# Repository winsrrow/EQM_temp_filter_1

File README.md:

# EQM_temp_filter_1
 
 ### Proyecto actualmente paralizado
 
 Proyecto para la actualización de la placa del laboratorio de sistemas y equipos de medida.

Este proyecto se compone de dos circuitos que servirán para la base de los ejercicios de laboratorio.
Para el diseño de esta placa me basaré en los esquemas de los que dispongo proporcionados por la profesora, si bien se pretende
añadir diversas modificaciones para facilitar el entendimiento y el uso, entre otras se añadirá protecciones contra polaridad inversa
e indicadores mediante LEDs.

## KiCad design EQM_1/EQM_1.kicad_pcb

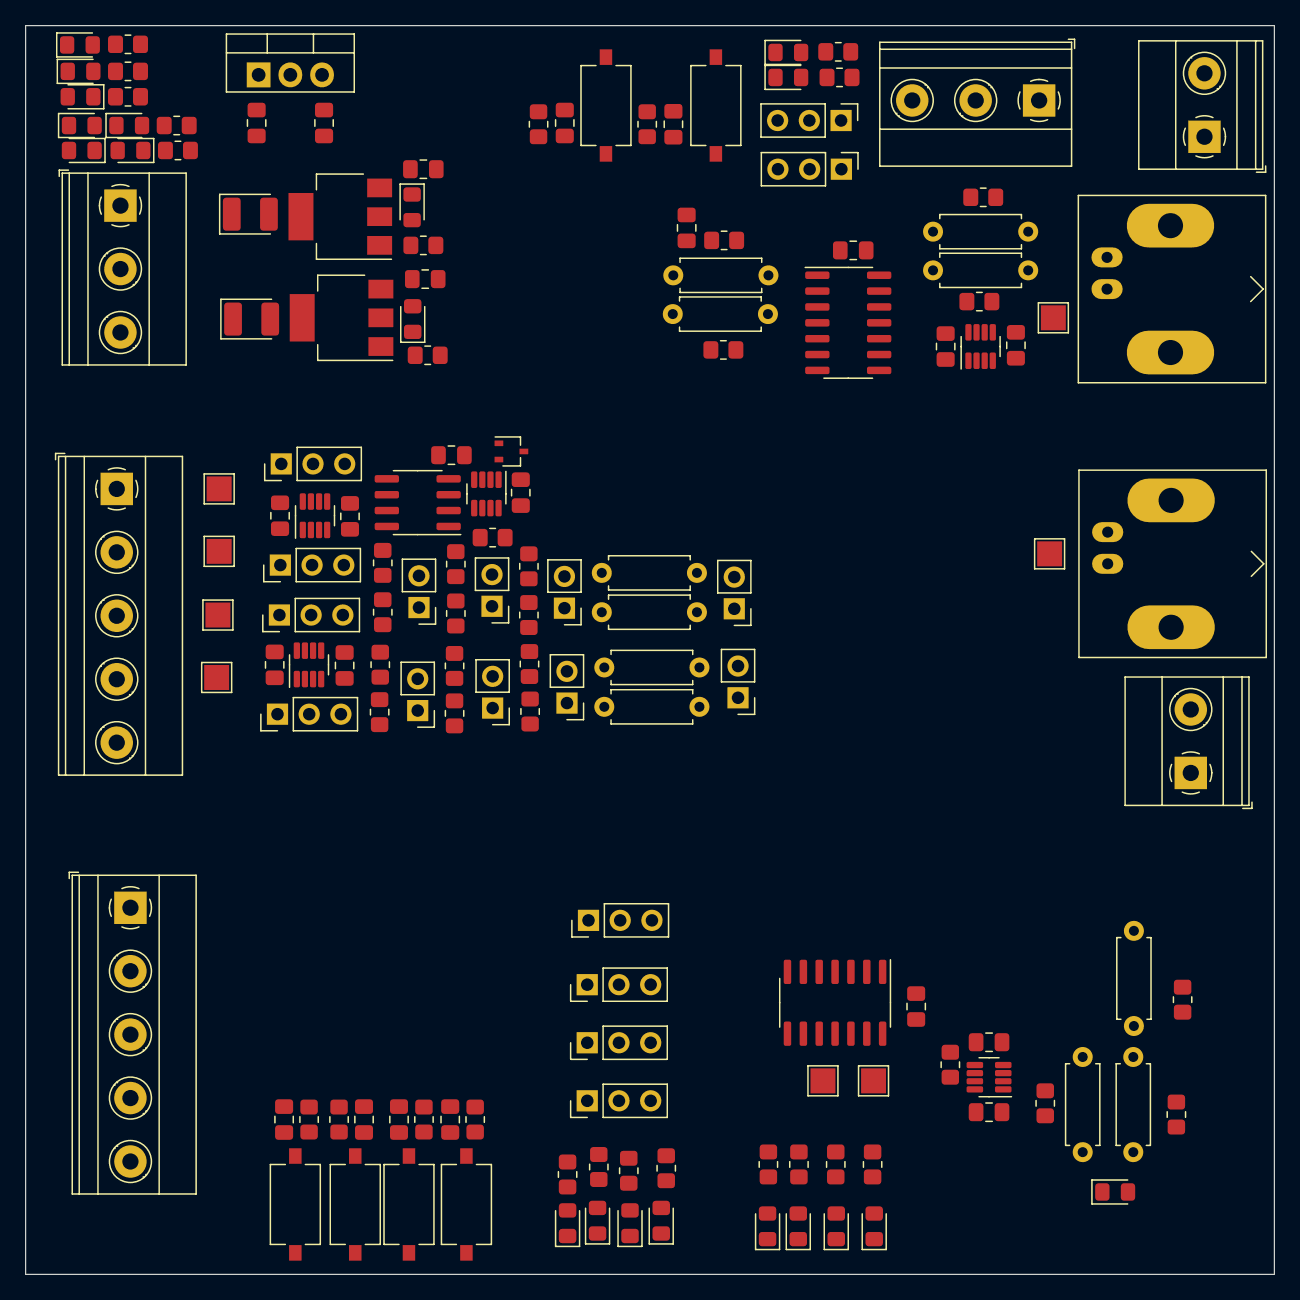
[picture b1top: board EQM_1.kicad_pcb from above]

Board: 2 copper layers, 100.0 x 100.0 mm, 152 parts (0 on the bottom side), 83 nets, no tracks yet.

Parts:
C201, C202, C203, C204: 3.3uF; C_0805_2012Metric_Pad1.18x1.45mm_HandSolder
C301, C302, C303, C304, C305, C306, C401, C402, C403, C404, C405, C406, C501, C502, C503, C504, C505, C506, C507: 100nF; C_0805_2012Metric_Pad1.18x1.45mm_HandSolder
D201, D209: 5.1V; D_0805_2012Metric_Pad1.15x1.40mm_HandSolder
D202, D203, D204, D207, D208, D401, D402, D502, D503, D504, D505, D506, D507, D508, D509: LED_Filled; D_0805_2012Metric_Pad1.15x1.40mm_HandSolder
D205, D206: 1n4007; D_0805_2012Metric_Pad1.15x1.40mm_HandSolder
D501: D_Zener_Filled; D_0805_2012Metric_Pad1.15x1.40mm_HandSolder
F201, F202: 200mA; D_1210_3225Metric_Pad1.42x2.65mm_HandSolder
J201, J407: Screw_Terminal_01x03; TerminalBlock_Phoenix_MKDS-1,5-3-5.08_1x03_P5.08mm_Horizont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
J301, J307, J312, J313, J405, J406, J502, J503, J504, J505: PinHeader_1x03_P2.54mm_Vertical
J302, J501: Screw_Terminal_01x05; TerminalBlock_Phoenix_MKDS-1,5-5-5.08_1x05_P5.08mm_Horizont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
J303, J304, J305, J306, J308, J309, J310, J311: PinHeader_1x02_P2.54mm_Vertical
J401, J403: Conn_Coaxial; BNC_Amphenol_B6252HB-NPP3G-50_Horizontal
J402, J404: Screw_Terminal_01x02; TerminalBlock_Phoenix_MKDS-1,5-2-5.08_1x02_P5.08mm_Horizont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
Q201: Q_PMOS_GDSD; SOT-223
Q202: Q_NMOS_GDSD; SOT-223
R201, R203, R206, R207: 1K5; R_0805_2012Metric_Pad1.20x1.40mm_HandSolder
R202, R409, R410, R511, R512, R513, R514, R515, R516, R517, R518: 670R; R_0805_2012Metric_Pad1.20x1.40mm_HandSolder
R204, R205, R301, R302, R303, R306, R307, R308, R310, R311, R312, R314, R315, R316, R401, R403, R405, R407, R411, R412, R501, R503, R504, R505, R506, R507, R509, R519: 10K; R_0805_2012Metric_Pad1.20x1.40mm_HandSolder
R304, R309, R313, R317, R402, R404, R406, R408, R502, R508, R510: 10K; R_Axial_DIN0207_L6.3mm_D2.5mm_P7.62mm_Horizontal
R305: 18K; R_0805_2012Metric_Pad1.20x1.40mm_HandSolder
SW401, SW402, SW501, SW502, SW503, SW504: SW_Push; SW_Tactile_SPST_NO_Straight_CK_PTS636Sx25SMTRLFS
TP301, TP302, TP303, TP304, TP401, TP402, TP501, TP502: TestPoint_Flag; TestPoint_Pad_2.0x2.0mm
U201: LM7805_TO220; TO-220-3_Vertical
U301: LM35-D; SOIC-8_3.9x4.9mm_P1.27mm
U302, U303, U305, U402, U502: TL082; SOT-23-8
U304: SOT-323_SC-70
U401, U501: CD4066BM; SO-14_3.9x8.65mm_P1.27mm

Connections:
+5V: C202.1, C403.1, C506.1, R202.2, SW401.2, SW402.2, SW501.2, SW502.2, SW503.2, SW504.2, U201.3 (VO), U401.14 (V_{DD}), U501.14 (V_{DD})
/Filtro programable/CS_{1}: J405.1, J407.1
/Filtro programable/CS_{2}: J406.1, J407.2
/Filtro programable/SW_{1}: C405.1, J405.3, R411.1, SW401.1
/Filtro programable/SW_{2}: C406.1, J406.3, R412.1, SW402.1
/Filtro programable/Sig_{IN-Buff}: R405.1, R406.1, R407.1, R408.1, U402.6 (-), U402.7
/Filtro programable/Sig_{IN}: J401.1 (In), J402.1, TP401.1, U402.5 (+)
/Filtro programable/Sig_{Out}: C401.2, J403.1 (In), J404.1, R401.2, R402.2, R403.2, R404.2, TP402.1, U402.1
/Filtro programable/V-: C401.1, U401.1, U401.4, U401.9, U401.10, U402.2 (-)
/Filtro programable/V_{Control-1}: J405.2, R410.1, U401.6, U401.13
/Filtro programable/V_{Control-2}: J406.2, R409.1, U401.5, U401.12
/Sección c/CS_{1}: J501.1, J502.1
/Sección c/CS_{2}: J501.2, J503.1
/Sección c/CS_{3}: J501.3, J504.1
/Sección c/CS_{4}: J501.4, J505.1
/Sección c/SW_{1}: C501.1, J502.3, R503.1, SW501.1
/Sección c/SW_{2}: C502.1, J503.3, R504.1, SW502.1
/Sección c/SW_{3}: C503.1, J504.3, R505.1, SW503.1
/Sección c/SW_{4}: C504.1, J505.3, R506.1, SW504.1
/Sección c/V_{Control-1}: J502.2, R518.1, U501.6, U501.13
/Sección c/V_{Control-2}: J503.2, R517.1, U501.5, U501.12
/Sección c/V_{Control-3}: J504.2, R516.1
/Sección c/V_{Control-4}: J505.2, R515.1
/Sensor de temperatura/L_{ratio-Buff}: J313.1, U305.1, U305.2 (-)
/Sensor de temperatura/L_{ratio-Out}: J302.4, J313.2, TP304.1
/Sensor de temperatura/L_{ratio}: J308.1, J309.1, J310.1, J311.1, J313.3, U305.3 (+)
/Sensor de temperatura/U_{ratio-Buff}: J307.1, U303.1, U303.2 (-)
/Sensor de temperatura/U_{ratio-Out}: J302.2, J307.2, TP302.1
/Sensor de temperatura/U_{ratio}: J303.1, J304.1, J305.1, J306.1, J307.3, U303.3 (+)
/Sensor de temperatura/V_{1-Buff}: J301.1, U303.6 (-), U303.7
/Sensor de temperatura/V_{1-Out}: J301.2, J302.1, TP301.1
/Sensor de temperatura/V_{1}: J301.3, R301.1, R302.1, R303.1, R304.1, U302.6 (-), U302.7, U303.5 (+)
/Sensor de temperatura/V_{2.5}: U301.4 (GND), U302.3 (+), U304.2 (K)
/Sensor de temperatura/V_{REF-Out}: J302.3, J312.2, TP303.1
/Sensor de temperatura/V_{REF_Buff}: J312.1, U305.6 (-), U305.7
/Sensor de temperatura/V_{REF}: J312.3, R306.2, R307.2, R308.2, R309.2, R310.1, R311.1, R312.1, R313.1, U302.1, U302.2 (-), U305.5 (+)
GND: C201.2, C202.2, C203.2, C204.1, C301.2, C302.2, C303.2, C304.1, C305.1, C306.1, C402.2, C403.2, C404.1, C405.2, C406.2, C501.2, C502.2, C503.2, C504.2, C505.2, C506.2, C507.1, D202.2 (A), D203.1 (K), D204.1 (K), D207.1 (K), D208.2 (A), D401.1 (K), D402.1 (K), D502.1 (K), D503.1 (K), D504.1 (K), D505.1 (K), D506.1 (K), D507.1 (K), D508.1 (K), D509.1 (K), J201.2, J302.5, J401.2 (Ext), J402.2, J403.2 (Ext), J404.2, J407.3, J501.5, R204.2, R205.1, R305.2, R314.2, R315.2, R316.2, R317.2, R411.2, R412.2, R503.2, R504.2, R505.2, R506.2, R519.2, U201.2 (GND), U304.1 (A), U401.7 (V_{SS}), U402.3 (+), U501.7 (V_{SS}), U502.3 (+), U502.5 (+), U502.6 (-)
unnamed: D201.2 (A), Q201.1 (G), R204.1
unnamed: D202.1 (K), D205.2 (A)
unnamed: D203.2 (A), R202.1
unnamed: D204.2 (A), R201.1
unnamed: D205.1 (K), R203.2
unnamed: D206.2 (A), R207.1
unnamed: D206.1 (K), D207.2 (A)
unnamed: D208.1 (K), R206.2
unnamed: D209.1 (K), Q202.1 (G), R205.2
unnamed: D401.2 (A), R409.2
unnamed: D402.2 (A), R410.2
unnamed: D501.2 (A), R507.2, R508.2, R509.1, R510.1, TP502.1
unnamed: D501.1 (K), R501.1, R502.1, TP501.1, U501.1, U501.4, U501.8, U501.11, U502.1
unnamed: D502.2 (A), R511.2
unnamed: D503.2 (A), R512.2
unnamed: D504.2 (A), R513.2
unnamed: D505.2 (A), R514.2
unnamed: D506.2 (A), R515.2
unnamed: D507.2 (A), R516.2
unnamed: D508.2 (A), R517.2
unnamed: D509.2 (A), R518.2
unnamed: F201.2, Q201.2 (D), Q201.4 (D)
unnamed: F202.2, Q202.2 (D), Q202.4 (D)
unnamed: F201.1, J201.1, R203.1
unnamed: F202.1, J201.3, R207.2
unnamed: J303.2, R301.2, R306.1
unnamed: J304.2, R302.2, R307.1
unnamed: J305.2, R303.2, R308.1
unnamed: J306.2, R304.2, R309.1
unnamed: J308.2, R310.2, R314.1
unnamed: J309.2, R311.2, R315.1
unnamed: J310.2, R312.2, R316.1
unnamed: J311.2, R313.2, R317.1
unnamed: R401.1, R402.1, U401.2
unnamed: R403.1, R404.1, U401.3
unnamed: R405.2, R406.2, U401.8
unnamed: R407.2, R408.2, U401.11
unnamed: R511.1, U501.10
unnamed: R512.1, U501.9
unnamed: R513.1, U501.3
unnamed: R514.1, U501.2
unnamed: R519.1, U502.7
unnamed: R305.1, U301.1 (V_{OUT}), U302.5 (+)
unnamed: R501.2, R502.2, R507.1, R508.1, U502.2 (-)
VCC: C201.1, C203.1, C301.1, C302.1, C303.1, C402.1, C505.1, D201.1 (K), Q201.3 (S), R201.2, U201.1 (VI), U301.8 (+V_{S}), U302.8 (V+), U303.8 (V+), U305.8 (V+), U402.8 (V+), U502.8 (V+)
VSS: C204.2, C304.2, C305.2, C306.2, C404.2, C507.2, D209.2 (A), Q202.3 (S), R206.1, R509.2, R510.2, U302.4 (V-), U303.4 (V-), U305.4 (V-), U402.4 (V-), U502.4 (V-)

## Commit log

2023-04-14 setup
2023-04-14 Temperatura
    Se ha añadido el circuito del sensor de temperatura
2023-04-15 Esquema finalizado
    El esquema está finalizado a falta de la asociación de footprints y la selección de valores para los pasivos
2023-04-15 PCB-1
    Primer posicionamiento de los componentes en la pcb y ligeros cambios en el esquemático.
    Posicionamiento MUY BASTO, simplemente para ver que los componentes caben en las dimensiones de la pcb elegida.
